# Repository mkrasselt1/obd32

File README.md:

# obd32
The goal of this project is to create a esp32 based pcb and software to
catch and submit automotive data from obd2 ports of supported vehicles 
to a given (list of ) endpoints(s). 

Anyone is free to join our goal to make the hardware reliable and affordable.

current plan conatins the featureset of:

    - esp32 based microprocessor
    - direct canbus via tranciever chip MCP2562-e
    - db9 for obd2 connection
    - wifi connection to hotsport or
    - onboard switchable usb port for lte-wifi-router 
    - ~~bluetooth connection compatible with elm327ds~~
    - micro sd card slot for configuration, logging and cache
    - ota updates via github releases
    - build in webfrontend
    - low power sleep mode (canbus activity and battery voltage)
    - gps for location and altitude sync
    - communication protocolls: https-post, websocket, mqtt

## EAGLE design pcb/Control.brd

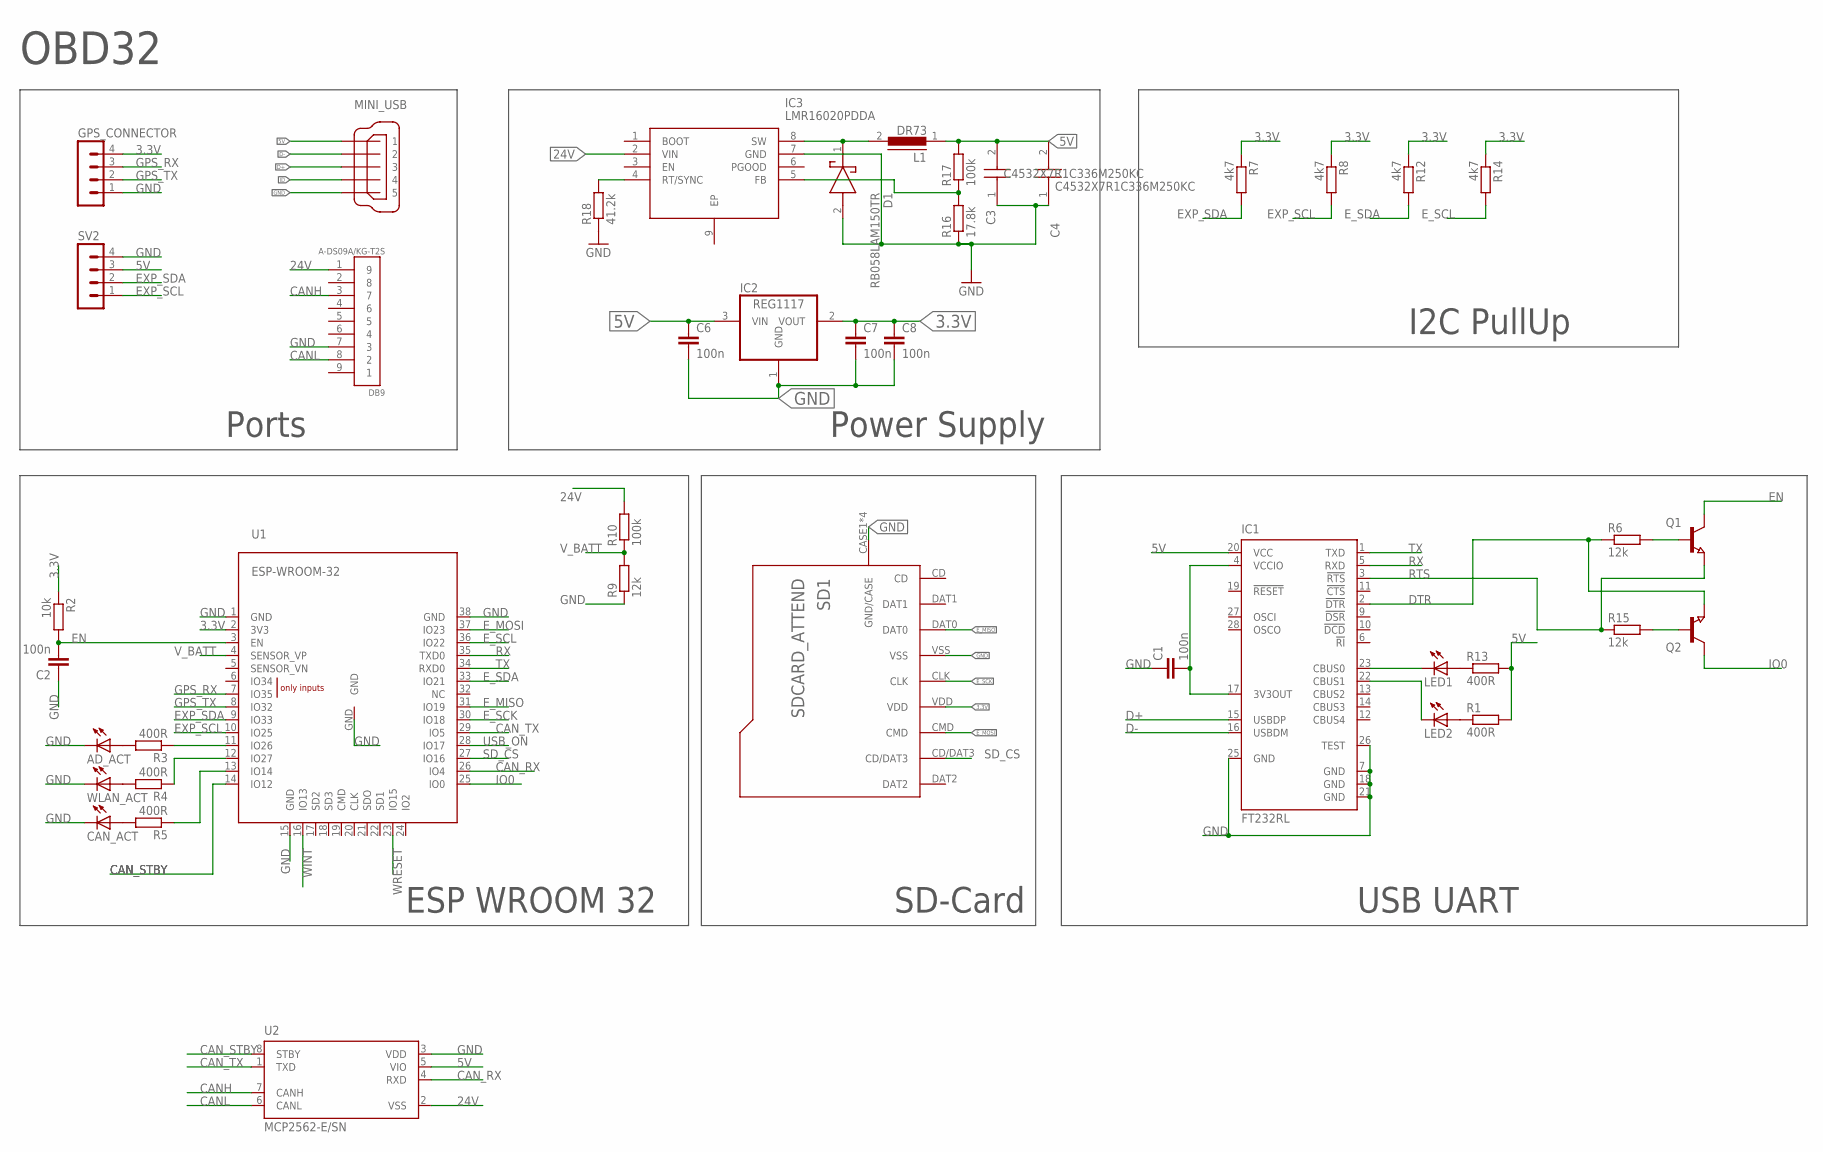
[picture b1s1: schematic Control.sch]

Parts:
AD_ACT: LEDCHIP-LED0805; CHIP-LED0805
C1, C2, C6, C7, C8: 100n; C0805
C3, C4: C4532X7R1C336M250KC; CAPC4532X360N
CAN_ACT: LEDCHIP-LED0805; CHIP-LED0805
D1: RB058LAM150TR; SODFL4725X105N
DB9: A-DS09A/KG-T2S
GPS_CONNECTOR: MA04-1
IC1: FT232RL; SSOP28
IC2: REG1117; SOT223
IC3: LMR16020PDDA; SOIC127P600X170-9N
L1: DR73
LED1, LED2: LEDCHIPLED_0805; CHIPLED_0805
MINI_USB: MINI-USB-32005-301; 32005-301
Q1, Q2: NPN-TRANSISTOR_SOT23; SOT23
R1, R3, R4, R5, R13: 400R; R0805
R2: 10k; R0805
R6, R9, R15: 12k; R0805
R7, R8, R12, R14: 4k7; R0805
R10, R17: 100k; R0805
R16: 17.8k; R0805
R18: 41.2k; R0805
SD1: SDCARD_ATTEND; SD_ATTEND
SV2: MA04-1
U1: ESP-WROOM-32
U2: MCP2562-E/SN; SOIC127P600X175-8N
WLAN_ACT: LEDCHIP-LED0805; CHIP-LED0805

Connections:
3.3V: C7.1, C8.1, GPS_CONNECTOR.4, IC2.2 (VOUT), R2.1, R7.1, R8.1, R12.1, R14.1, SD1.VDD, U1.2 (3V3)
5V: C3.2, C4.2, C6.1, IC1.20 (VCC), IC2.3 (VIN), L1.1, MINI_USB.1, R1.2, R13.2, R17.2, SV2.3, U2.5 (VIO)
24V: DB9.1 (9), IC3.2 (VIN), R10.2, U2.2 (VSS)
CANH: DB9.3 (7), U2.7 (CANH)
CANL: DB9.8 (2), U2.6 (CANL)
CAN_RX: U1.26 (IO4), U2.4 (RXD)
CAN_STBY: U1.14 (IO12), U2.8 (STBY)
CAN_TX: U1.29 (IO5), U2.1 (TXD)
D+: IC1.15 (USBDP), MINI_USB.3
D-: IC1.16 (USBDM), MINI_USB.2
DTR: IC1.2 (!DTR), Q2.2 (E), R6.1
EN: C2.2, Q1.3 (C), R2.2, U1.3 (EN)
EXP_SCL: R8.2, SV2.1, U1.10 (IO25)
EXP_SDA: R7.2, SV2.2, U1.9 (IO33)
E_MISO: SD1.DAT0, U1.31 (IO19)
E_MOSI: SD1.CMD, U1.37 (IO23)
E_SCK: SD1.CLK, U1.30 (IO18)
E_SCL: R14.2, U1.36 (IO22)
E_SDA: R12.2, U1.33 (IO21)
GND: AD_ACT.C, C1.1, C2.1, C3.1, C4.1, C6.2, C7.2, C8.2, CAN_ACT.C, D1.2 (A), DB9.7 (3), GPS_CONNECTOR.1, IC1.7 (GND), IC1.18 (GND), IC1.21 (GND), IC1.25 (GND), IC1.26 (TEST), IC2.1 (GND), IC3.7 (GND), MINI_USB.5, R9.1, R16.1, R18.1, SD1.CASE1 (GND/CASE), SD1.CASE2 (GND/CASE), SD1.CASE3 (GND/CASE), SD1.CASE4 (GND/CASE), SD1.VSS, SV2.4, U1.1 (GND), U1.15 (GND), U1.38 (GND), U1.GND, U2.3 (VDD), WLAN_ACT.C
GPS_RX: GPS_CONNECTOR.3, U1.7 (IO35)
GPS_TX: GPS_CONNECTOR.2, U1.8 (IO32)
ID: MINI_USB.4
IO0: Q2.3 (C), U1.25 (IO0)
unnamed: IC1.23 (CBUS0), LED1.C
unnamed: IC3.5 (FB), R16.2, R17.1
unnamed: Q1.1 (B), R6.2
unnamed: C1.2, IC1.4 (VCCIO), IC1.17 (3V3OUT)
unnamed: Q2.1 (B), R15.2
unnamed: AD_ACT.A, R3.2
unnamed: R3.1, U1.11 (IO26)
unnamed: IC1.22 (CBUS1), LED2.C
unnamed: LED1.A, R13.1
unnamed: D1.1 (K), IC3.8 (SW), L1.2
unnamed: LED2.A, R1.1
unnamed: R4.2, WLAN_ACT.A
unnamed: R4.1, U1.12 (IO27)
unnamed: CAN_ACT.A, R5.2
unnamed: R5.1, U1.13 (IO14)
unnamed: IC3.4 (RT/SYNC), R18.2
RTS: IC1.3 (!RTS), Q1.2 (E), R15.1
RX: IC1.5 (RXD), U1.35 (TXD0)
SD_CS: SD1.CD/DAT3, U1.27 (IO16)
TX: IC1.1 (TXD), U1.34 (RXD0)
USB_ON: U1.28 (IO17)
V_BATT: R9.2, R10.1, U1.4 (SENSOR_VP)
WINT: U1.16 (IO13)
WRESET: U1.23 (IO15)

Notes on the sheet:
Power Supply
Ports
USB UART
SD-Card
ESP WROOM 32
OBD32
I2C PullUp

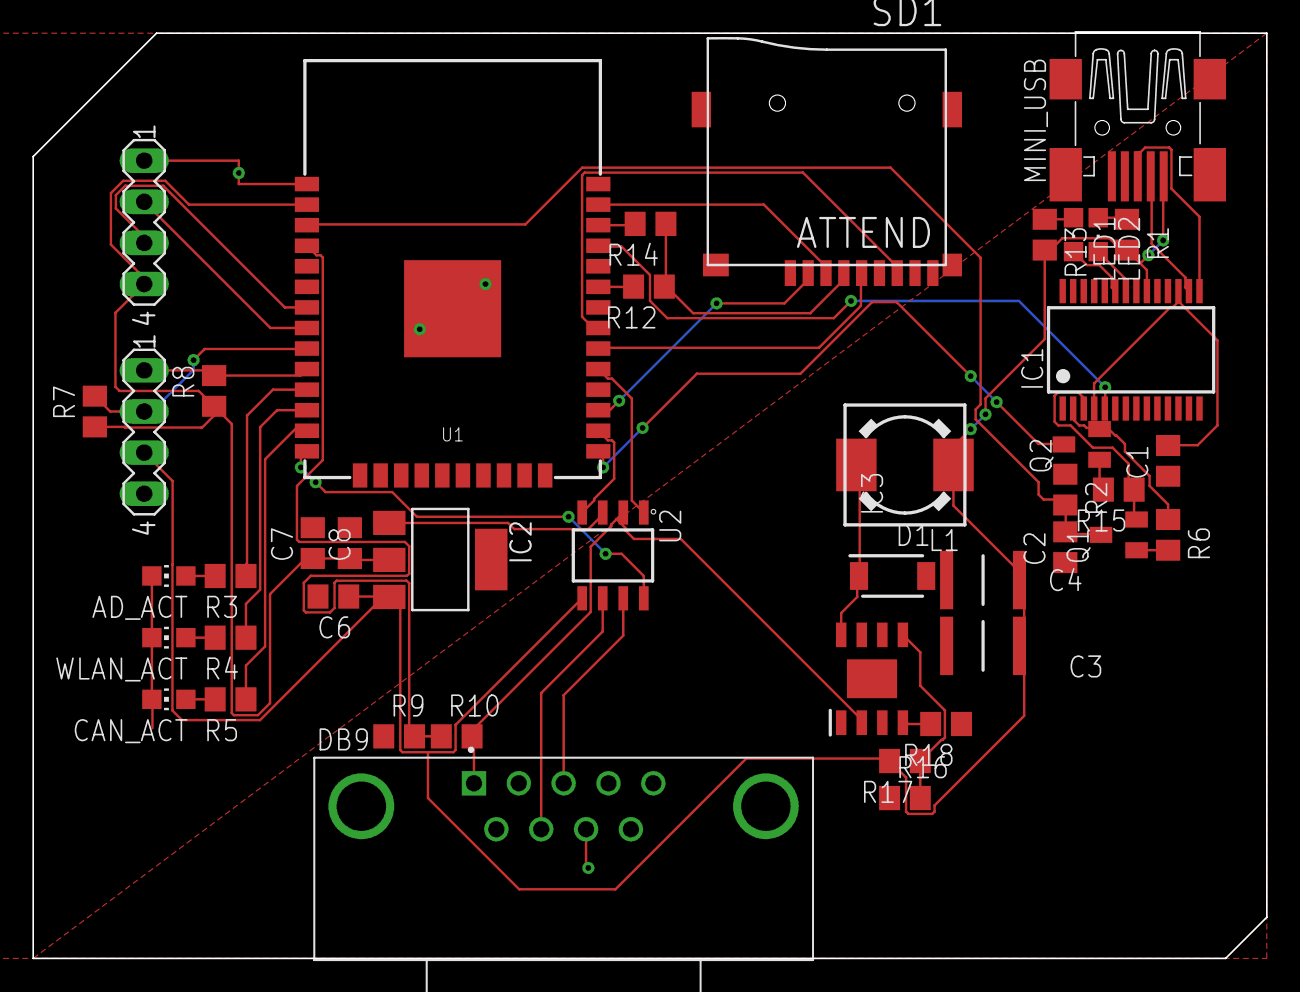
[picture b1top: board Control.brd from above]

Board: 2 copper layers, 76.2 x 57.1 mm, 43 parts (0 on the bottom side), 44 nets.

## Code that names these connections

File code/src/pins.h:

// vv GPIO number vv
#define GPIO_UART_RX 3		// UART0
#define GPIO_UART_TX 1		// UART0
#define GPIO_GPS_RX 15		// UART2
#define GPIO_GPS_TX 2		// UART2
#define GPIO_CAN_RX 14		// CAN
#define GPIO_CAN_TX 12		// CAN
#define GPIO_I2C0_SDA 22	// I2C
#define GPIO_I2C0_SCL 23	// I2C
#define GPIO_ADC 36 		// ADC1_CH0
#define GPIO_BTN1 26		// ESP32_MISC
#define GPIO_USB_EN 18
#define GPIO_LED_R 4
#define GPIO_LED_G 16
#define GPIO_LED_B 17
#define GPIO_CS_SDCARD 4    // Chip Select SD Card

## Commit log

2020-11-02 Add: Readme Project Description \n Add: Basic PCB Design
2020-11-02 Fix: readme markdown correction
2020-11-02 Add: basic pio project
2020-11-09 FIX: Simple ODB2 Scanner
2020-11-09 Add: Simple MQTT Client
2020-11-13 adjust pio to my platform
2020-11-14 first prototype of decoder
2020-11-28 working prototype of ISO-TP- and car decoder
2020-11-29 1st draft
2020-11-30 Maybe version of board
2020-12-02 Board: Add USB-C and CP2102 UART converter
2020-12-02 Board: Add cuttable solder jumper to allow disconnection from 12V rail
2020-12-03 Board: replace pressure sensor with more common bmp280
2020-12-07 Add header for pin mapping; put stuff into main
2020-12-07 Board: some refinement; Add button BOOT0
2020-12-27 PIO: use hopefulle fitting board
2020-12-27 OBD: Work towards generic decoder
2021-02-21 Add: Base Code Send SOC to EVNotify
2021-02-21 Fix: Revert car_decode out of obd file, merge mistake
2021-02-21 PCB: Move components from bottom to top side of board. Move SD-card slot to sub board. Add SAM-M8N GPS-receiver
2021-02-22 Add: Extended and Location Sync Messages to EvNotify Sender
2021-02-25 BMP280 was replaced with BMP388, adjust code accordingly
2021-02-26 Add: Seperate Threads for GPS and Backend
2021-03-07 Board: use different USB-C Receptable
2021-03-07 Board: add Gerber files
2021-06-03 Board: Adjustments
2021-11-10 Update README.md
    Fixed markdown of readme
2022-01-23 Moved prototype code to main.old; Add: OTA Update Capabilitys; Add: WEB Interface with events and websocket server Add: OTA Web Interface
2026-04-27 ci: auto-mirror to GitLab

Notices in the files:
pcb/Control.brd:
©2020 Julius Schneider
